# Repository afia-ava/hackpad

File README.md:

# hackpad

I designed a Hackpad using KiCad. This project involved schematic design, PCB layout, and 3D Design using Fusion 360. 

**Stack**  
KiCad (schematic + PCB)
Custom PCB design

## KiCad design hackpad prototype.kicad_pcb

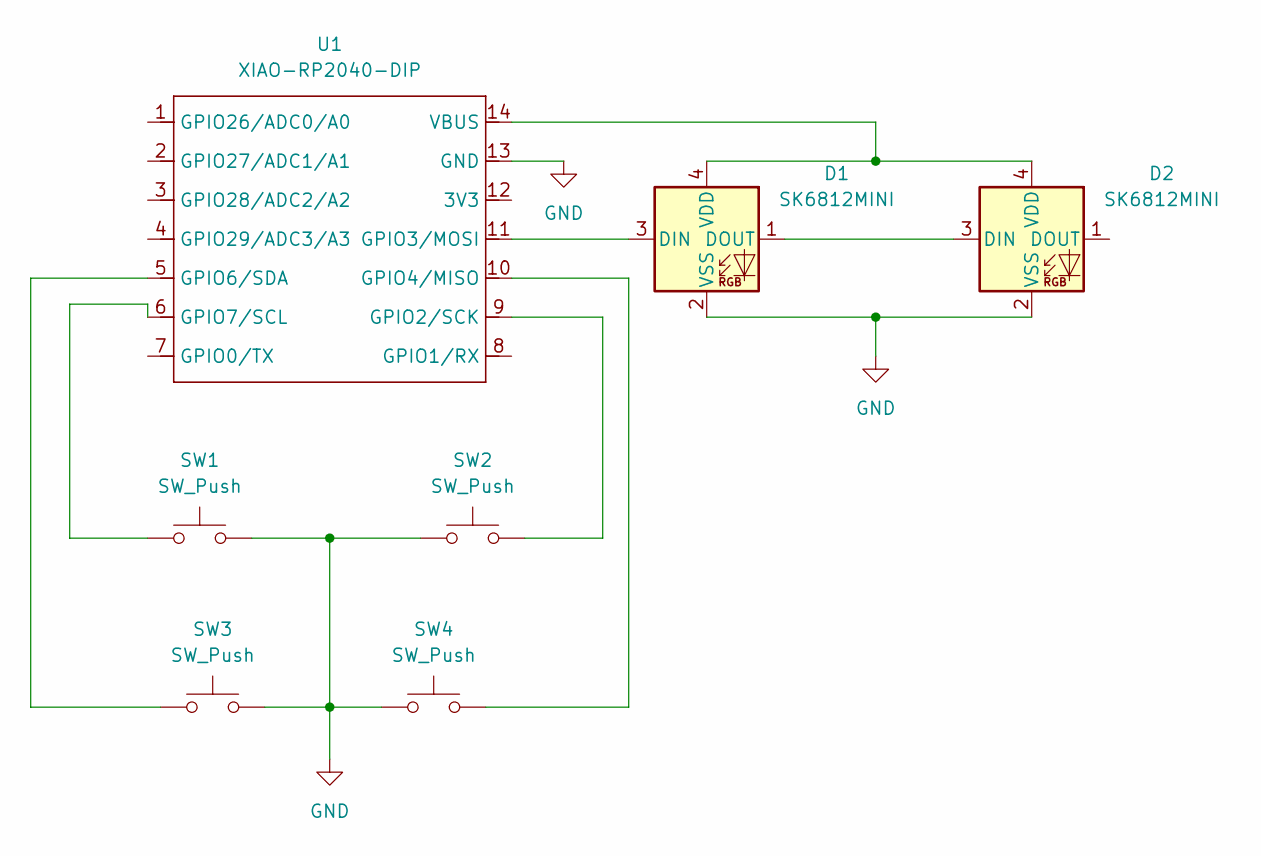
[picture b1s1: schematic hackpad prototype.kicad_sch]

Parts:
D1, D2: SK6812MINI; LED_SK6812MINI_PLCC4_3.5x3.5mm_P1.75mm
SW1, SW2, SW3, SW4: SW_Push; SW_Cherry_MX_1.00u_PCB
U1: XIAO-RP2040-DIP

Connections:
GND: D1.2 (VSS), D2.2 (VSS), SW1.2, SW2.1, SW3.2, SW4.1, U1.13 (GND)
unnamed: D1.3 (DIN), U1.11 (GPIO3/MOSI)
unnamed: D1.1 (DOUT), D2.3 (DIN)
unnamed: D1.4 (VDD), D2.4 (VDD), U1.14 (VBUS)
unnamed: SW2.2, U1.9 (GPIO2/SCK)
unnamed: SW4.2, U1.10 (GPIO4/MISO)
unnamed: SW3.1, U1.5 (GPIO6/SDA)
unnamed: SW1.1, U1.6 (GPIO7/SCL)

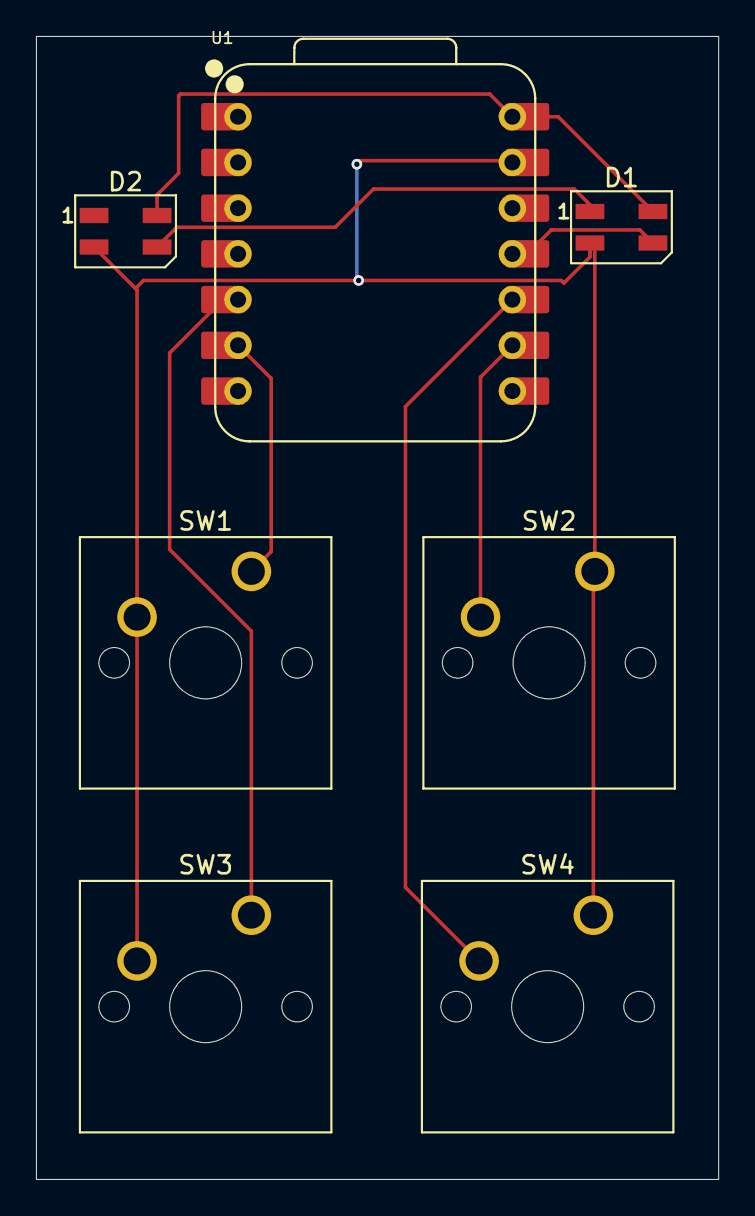
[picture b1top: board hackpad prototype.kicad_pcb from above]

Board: 2 copper layers, 37.9 x 63.5 mm, 7 parts (0 on the bottom side), 8 nets.

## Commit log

2026-01-13 README with project details and stack
2026-01-13 pcb file
2026-01-13 schematic file for hackpad
2026-03-31 Create sample image
2026-03-31 add hackapd images
    Added images of the Hackpad to the README.
